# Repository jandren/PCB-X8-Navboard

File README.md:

# PCB-X8-Navboard
IMU, Pressure sensor and Sonar driver

PCB

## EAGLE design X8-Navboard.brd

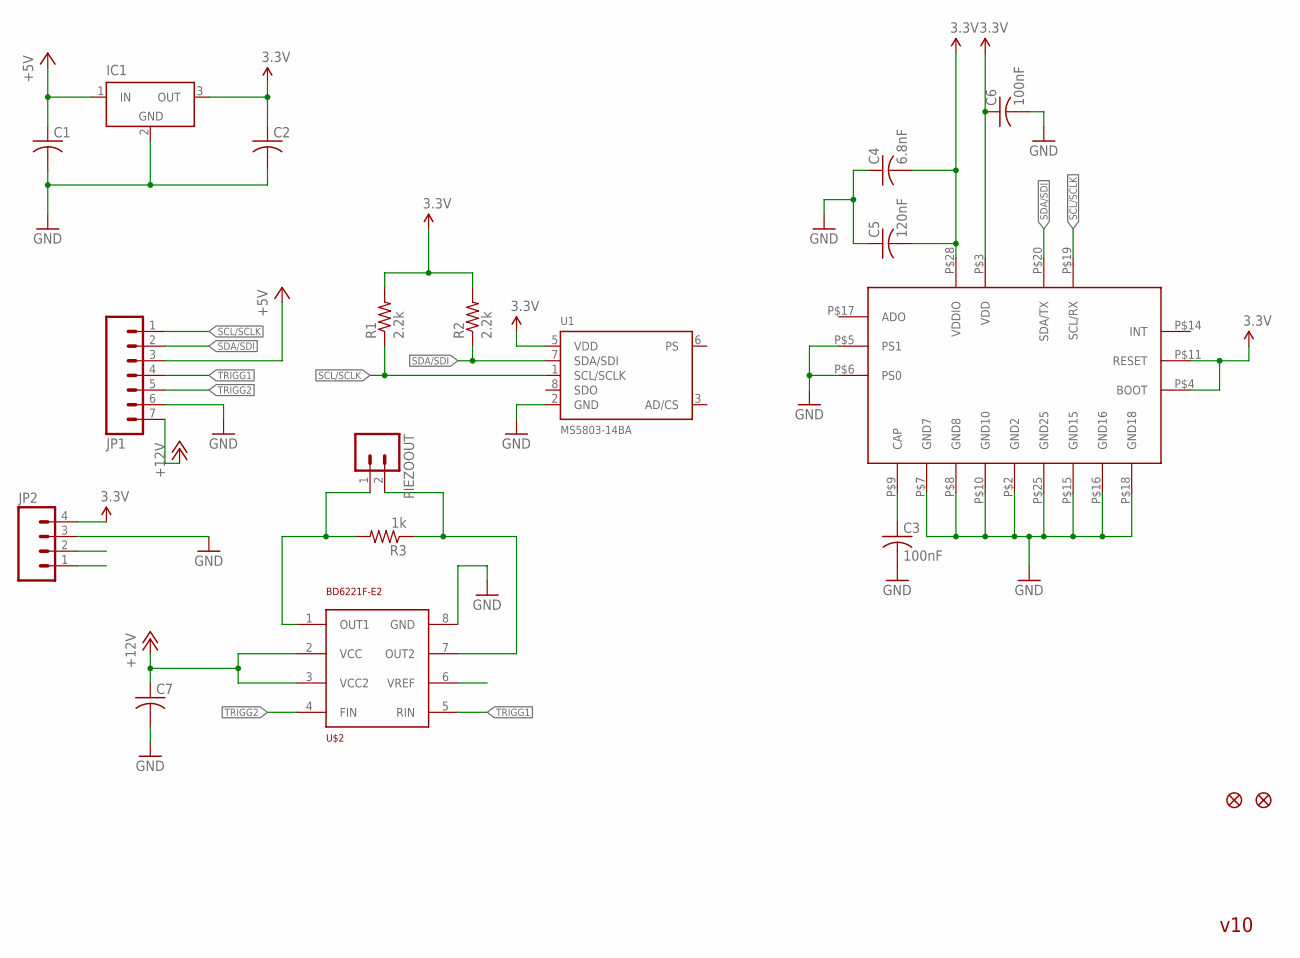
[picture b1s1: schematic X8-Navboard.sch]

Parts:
C1, C2, C7: C-USC0603; C0603
C3, C6: 100nF; C0603
C4: 6.8nF; C0603
C5: 120nF; C0603
FID1, FID2: FIDUCIAL1X2; FIDUCIAL-1X2
IC1: LT1129CST5; SOT223
JP1: M07; 1X07
JP2: M04NO_SILK_ALL_ROUND; 1X04_NO_SILK_ALL_ROUND
PIEZOOUT: M02LOCK_LONGPADS; 1X02_LOCK_LONGPADS
R1, R2: 2.2k; 0603-RES
R3: 1k; 0603-RES
U1: MS5803-14BA; MS5803
U$1: BNO055; LGA28
U$2: BD6221F-E2; SOIC8

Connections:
3.3V: C2.1, C4.2, C5.2, C6.1, IC1.3 (OUT), JP2.4, R1.2, R2.2, U1.5 (VDD), U$1.P$3 (VDD), U$1.P$4 (BOOT), U$1.P$11 (RESET), U$1.P$28 (VDDIO)
+5V: C1.1, IC1.1 (IN), JP1.3
+12V: C7.1, JP1.7, U$2.2 (VCC), U$2.3 (VCC2)
GND: C1.2, C2.2, C3.2, C4.1, C5.1, C6.2, C7.2, IC1.2 (GND), IC1.4 (GND), JP1.6, JP2.3, U1.2 (GND), U$1.P$2 (GND2), U$1.P$5 (PS1), U$1.P$6 (PS0), U$1.P$7 (GND7), U$1.P$8 (GND8), U$1.P$10 (GND10), U$1.P$15 (GND15), U$1.P$16 (GND16), U$1.P$18 (GND18), U$1.P$25 (GND25), U$2.8 (GND)
unnamed: PIEZOOUT.1, R3.2, U$2.1 (OUT1)
unnamed: PIEZOOUT.2, R3.1, U$2.7 (OUT2)
unnamed: C3.1, U$1.P$9 (CAP)
SCL/SCLK: JP1.1, JP2.1, R1.1, U1.1 (SCL/SCLK), U$1.P$19 (SCL/RX)
SDA/SDI: JP1.2, JP2.2, R2.1, U1.7 (SDA/SDI), U$1.P$20 (SDA/TX)
TRIGG1: JP1.4, U$2.5 (RIN)
TRIGG2: JP1.5, U$2.4 (FIN)

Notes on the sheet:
v10

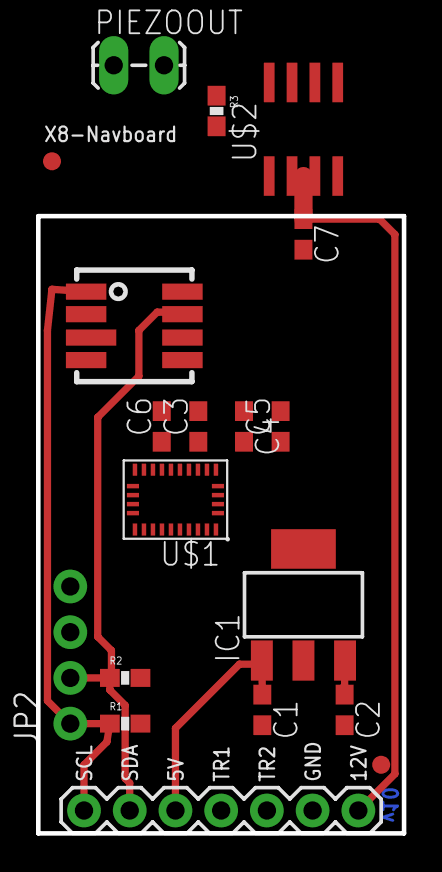
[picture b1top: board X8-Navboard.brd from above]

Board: 2 copper layers, 20.3 x 34.3 mm, 19 parts (0 on the bottom side), 11 nets.

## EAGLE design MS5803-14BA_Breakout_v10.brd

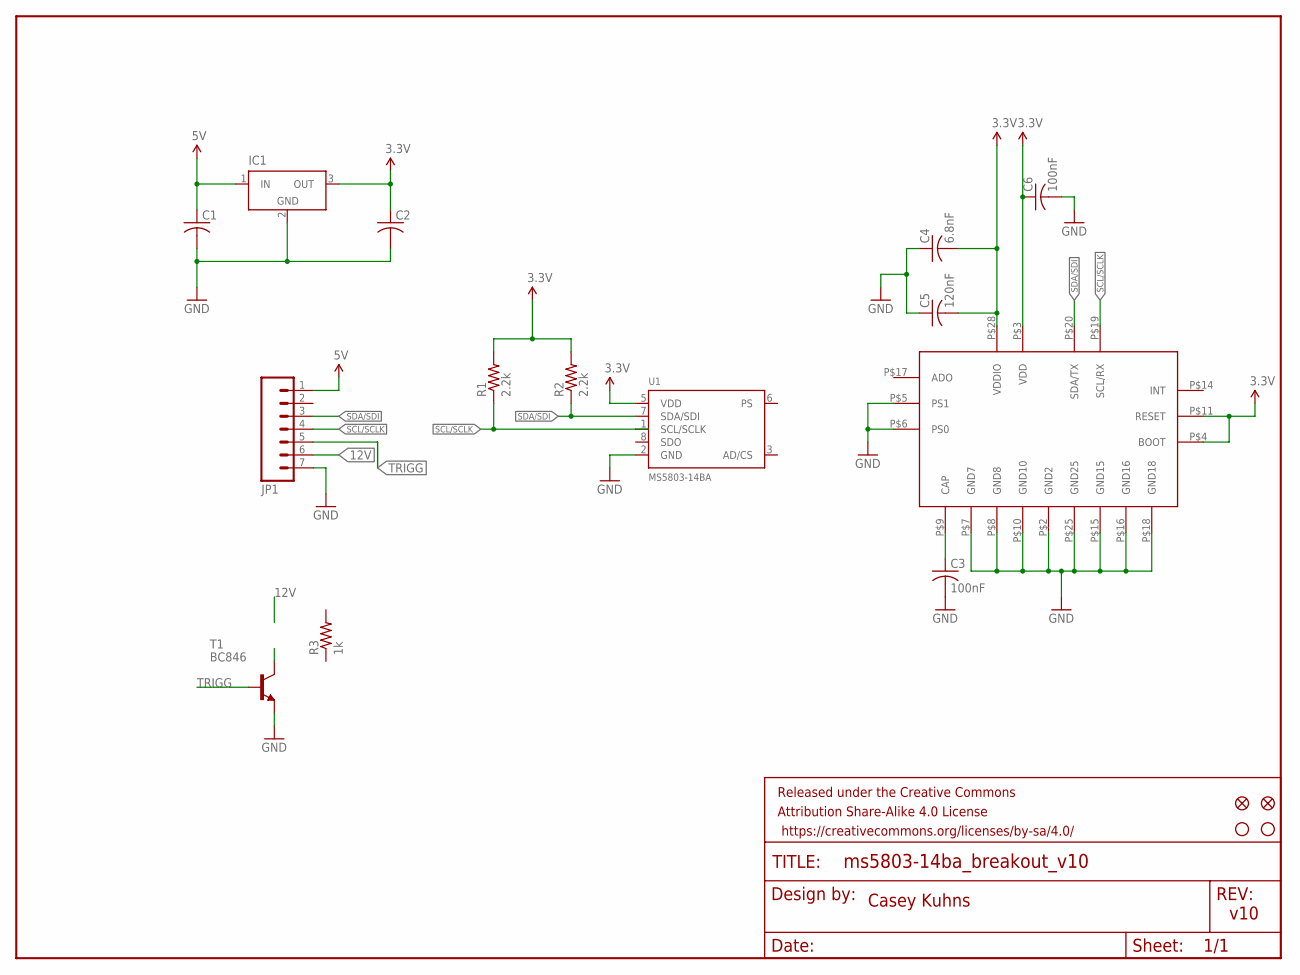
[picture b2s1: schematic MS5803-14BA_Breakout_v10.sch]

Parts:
C1, C2: C-USC0603; C0603
C3, C6: 100nF; C0603
C4: 6.8nF; C0603
C5: 120nF; C0603
FID1, FID2: FIDUCIAL1X2; FIDUCIAL-1X2
FRAME1: FRAME-LETTER; CREATIVE_COMMONS
IC1: LT1129CST5; SOT223
JP1: M07; 1X07
R1, R2: 2.2k; 0603-RES
R3: 1k; 0603-RES
STANDOFF1, STANDOFF2: STAND-OFFTIGHT; STAND-OFF-TIGHT
T1: BC846; SOT23
U1: MS5803-14BA; MS5803
U$1: BNO055; LGA28

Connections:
3.3V: C1.1, C2.1, C4.2, C5.2, C6.1, IC1.1 (IN), IC1.3 (OUT), JP1.1, R1.2, R2.2, U1.5 (VDD), U$1.P$3 (VDD), U$1.P$4 (BOOT), U$1.P$11 (RESET), U$1.P$28 (VDDIO)
12V: JP1.6
GND: C1.2, C2.2, C3.2, C4.1, C5.1, C6.2, IC1.2 (GND), IC1.4 (GND), JP1.7, T1.2 (E), U1.2 (GND), U$1.P$2 (GND2), U$1.P$5 (PS1), U$1.P$6 (PS0), U$1.P$7 (GND7), U$1.P$8 (GND8), U$1.P$10 (GND10), U$1.P$15 (GND15), U$1.P$16 (GND16), U$1.P$18 (GND18), U$1.P$25 (GND25)
unnamed: C3.1, U$1.P$9 (CAP)
SCL/SCLK: JP1.4, R1.1, U1.1 (SCL/SCLK)
SDA/SDI: JP1.3, R2.1, U1.7 (SDA/SDI)
TRIGG: JP1.5

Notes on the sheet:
Casey Kuhns
v10

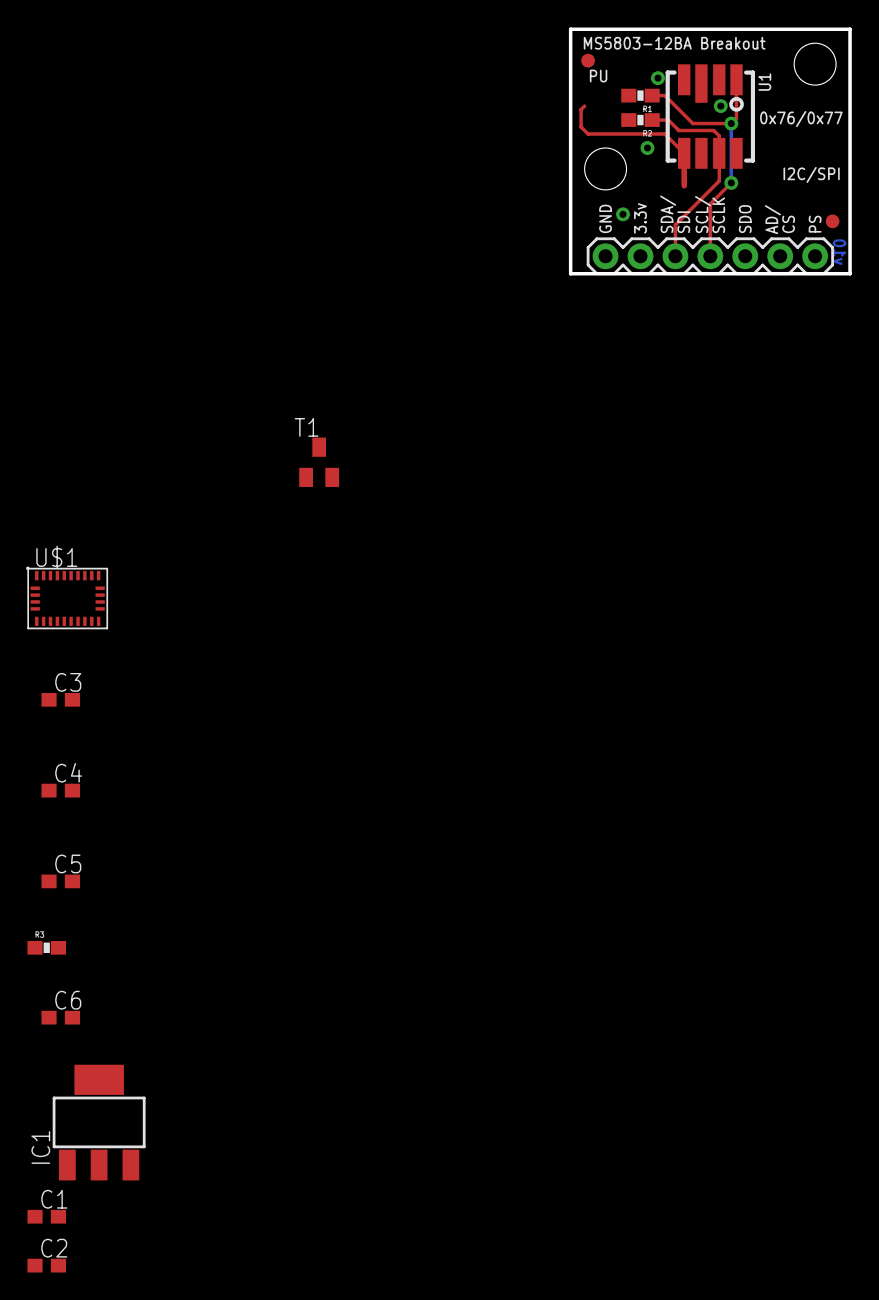
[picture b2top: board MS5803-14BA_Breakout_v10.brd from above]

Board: 2 copper layers, 20.3 x 17.8 mm, 19 parts (0 on the bottom side), 5 nets.

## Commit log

2016-02-11 intial commit
2016-02-11 Created readme
2016-02-11 "Starting with board layout"
2016-02-11 Start on board layout
2016-02-11 more layout work

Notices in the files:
parts and their libraries:
SparkFun-Aesthetics: Licensing: Creative Commons ShareAlike 4.0 International - https://creativecommons.org/licenses/by-sa/4.0
SparkFun-Aesthetics: Released under the Creative Commons Attribution Share-Alike 4.0 License
SparkFun-Aesthetics: https://creativecommons.org/licenses/by-sa/4.0
